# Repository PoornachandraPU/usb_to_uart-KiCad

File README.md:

# USB-to-UART Converter PCB

A USB-to-UART converter PCB designed using KiCad as a learning project to understand the basic PCB design workflow.

## Overview

The board uses the CP2102N USB-to-UART bridge to provide communication between a computer's USB interface and a microcontroller's UART interface.

The PCB uses a USB Type-C connector as the USB interface and provides an external UART header.

## Main Components

- CP2102N USB-to-UART bridge
- USB Type-C receptacle
- ESD protection diode
- SMD resistors and capacitors
- Status LEDs
- 5-pin UART header

## KiCad Design Workflow

- Schematic capture
- Component selection
- Footprint assignment
- Custom footprint/library integration
- PCB component placement
- PCB routing
- Via usage
- Ground plane
- Design Rule Checking (DRC)
- 3D PCB visualization

## Schematic

The circuit schematic showing the CP2102N USB-to-UART interface and its associated components.

## PCB Layout

The PCB layout showing component placement, track routing, vias, and ground plane.

## 3D View

3D visualization of the designed PCB, showing the component arrangement and board layout.

## Tools

- KiCad
- CP2102N USB-to-UART bridge

## Project Status and Limitations

Completed as a learning/prototype project to understand the basic KiCad PCB design workflow.

> **Note:** This project was developed as a learning exercise by following a guided tutorial. The PCB layout currently has some unresolved Design Rule Check (DRC) errors, mainly related to routing. These issues were not fully resolved during the project.

The design is intended for learning and portfolio demonstration and has not been validated for manufacturing or real-world hardware operation.

## Acknowledgement

This project was developed as a learning exercise based on a guided USB-to-UART PCB design tutorial. The design was recreated independently to gain practical exposure to KiCad schematic capture, component placement, PCB routing, and layout design.

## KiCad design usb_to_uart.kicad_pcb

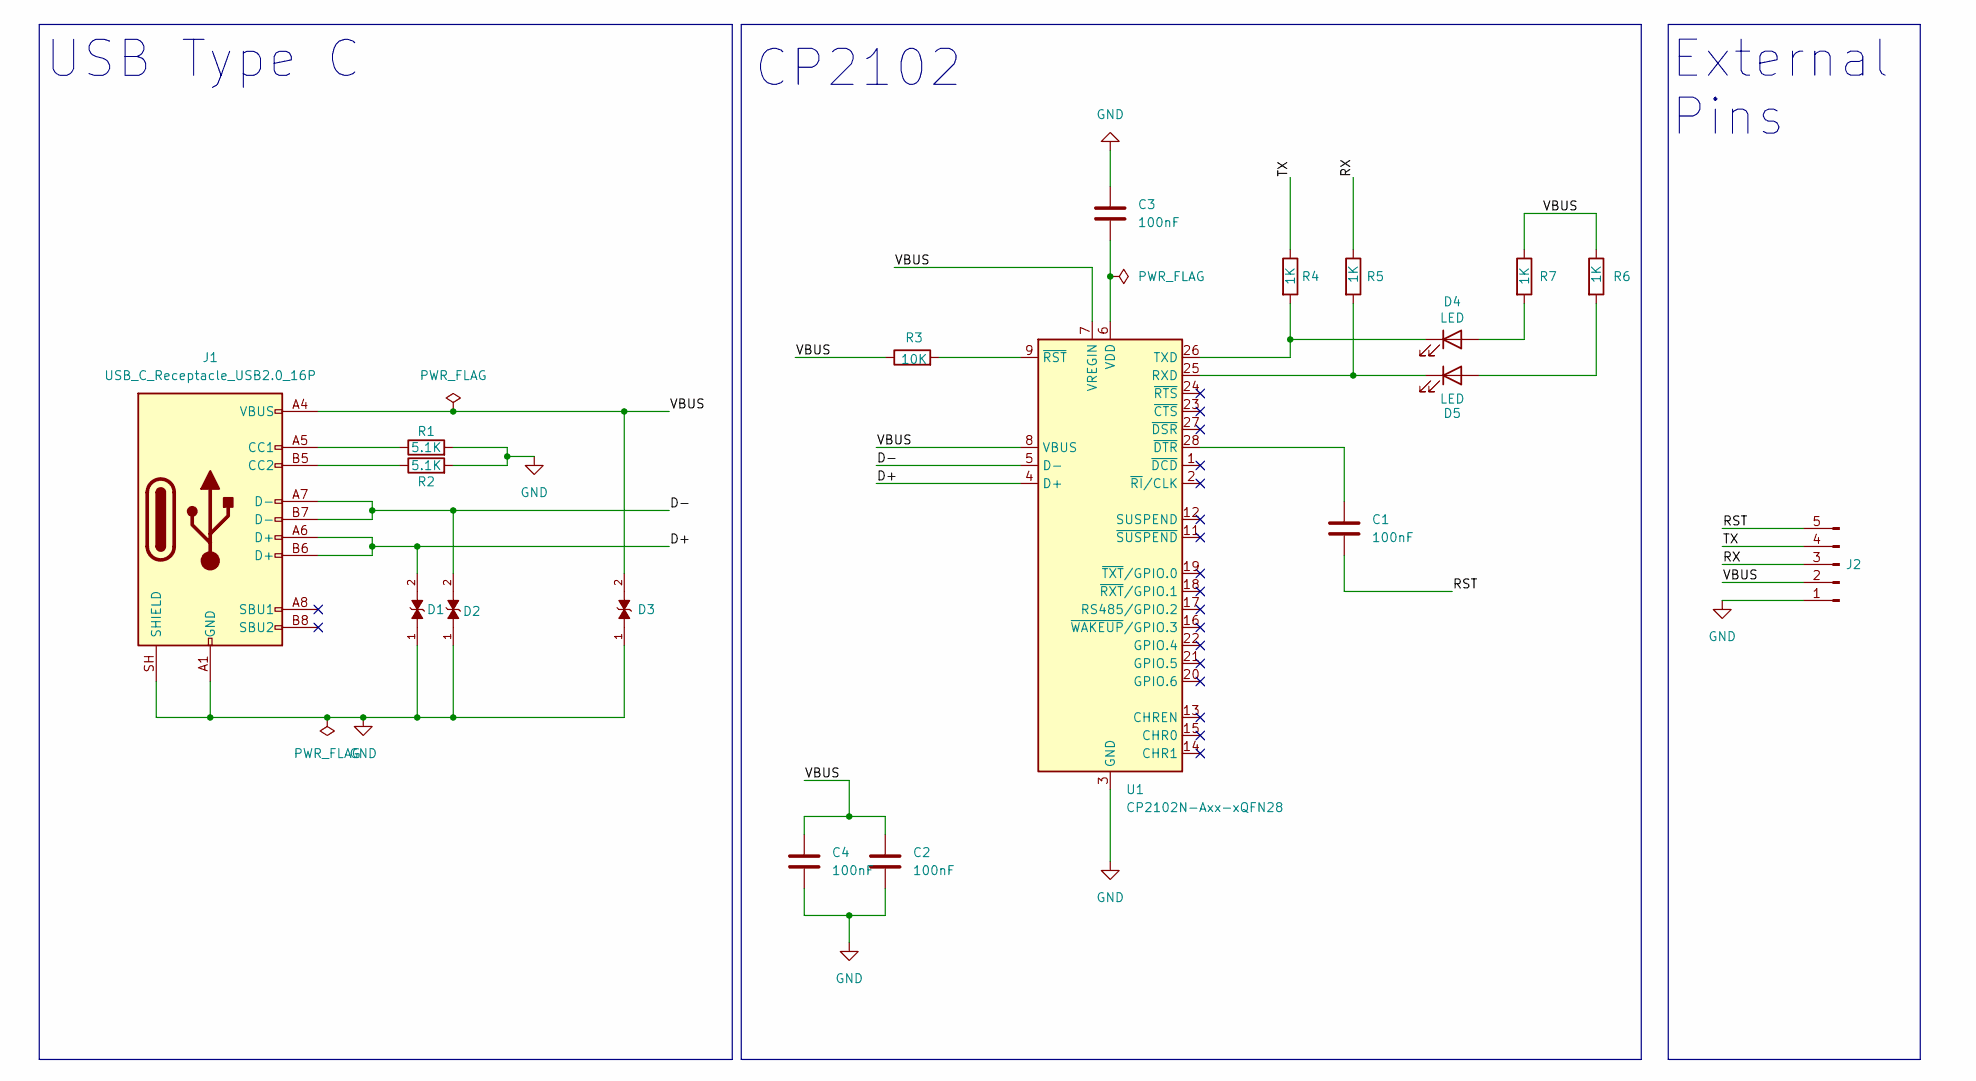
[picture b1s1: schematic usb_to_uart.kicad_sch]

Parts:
C1, C2, C3, C4: 100nF; C_0201_0603Metric
D1, D2, D3: LESD5D5.0CT1G; TVS_LESD5D5.0CT1G; PARTREV O
D4, D5: LED; LED_0201_0603Metric
J1: USB_C_Receptacle_USB2.0_16P; USB_C_Receptacle_HRO_TYPE-C-31-M-12
J2: Conn_01x05_Pin; PinHeader_1x05_P2.54mm_Horizontal
R1, R2: 5.1K; R_0201_0603Metric
R3: 10K; R_0201_0603Metric
R4, R5, R6, R7: 1K; R_0201_0603Metric
U1: CP2102N-Axx-xQFN28; QFN-28-1EP_5x5mm_P0.5mm_EP3.35x3.35mm

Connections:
/D+: D1.2, J1.A6 (D+), J1.B6 (D+), U1.4 (D+)
/D-: D2.2, J1.A7 (D-), J1.B7 (D-), U1.5 (D-)
/RST: C1.2, J2.5
/RX: J2.3, R5.1
/TX: J2.4, R4.1
/VBUS: C2.1, C4.1, D3.2, J1.A4 (VBUS), J1.A9 (VBUS), J1.B4 (VBUS), J1.B9 (VBUS), J2.2, R3.1, R6.1, R7.1, U1.7 (VREGIN), U1.8 (VBUS)
GND: C2.2, C3.1, C4.2, D1.1, D2.1, D3.1, J1.A1 (GND), J1.A12 (GND), J1.B1 (GND), J1.B12 (GND), J1.SH (SHIELD), J2.1, R1.2, R2.2, U1.3 (GND), U1.29 (GND)
unnamed: D4.2 (A), R7.2
unnamed: D4.1 (K), R4.2, U1.26 (TXD)
unnamed: D5.2 (A), R6.2
unnamed: D5.1 (K), R5.2, U1.25 (RXD)
unnamed: J1.A5 (CC1), R1.1
unnamed: J1.B5 (CC2), R2.1
unnamed: C3.2, U1.6 (VDD)
unnamed: C1.1, U1.28 (~DTR)
unnamed: R3.2, U1.9 (~RST)

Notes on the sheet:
USB Type C
External Pins
CP2102

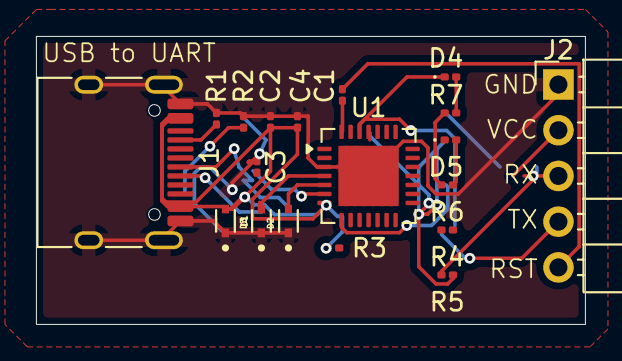
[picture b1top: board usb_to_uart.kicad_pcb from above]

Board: 2 copper layers, 30.5 x 16.0 mm, 19 parts (0 on the bottom side), 16 nets.
